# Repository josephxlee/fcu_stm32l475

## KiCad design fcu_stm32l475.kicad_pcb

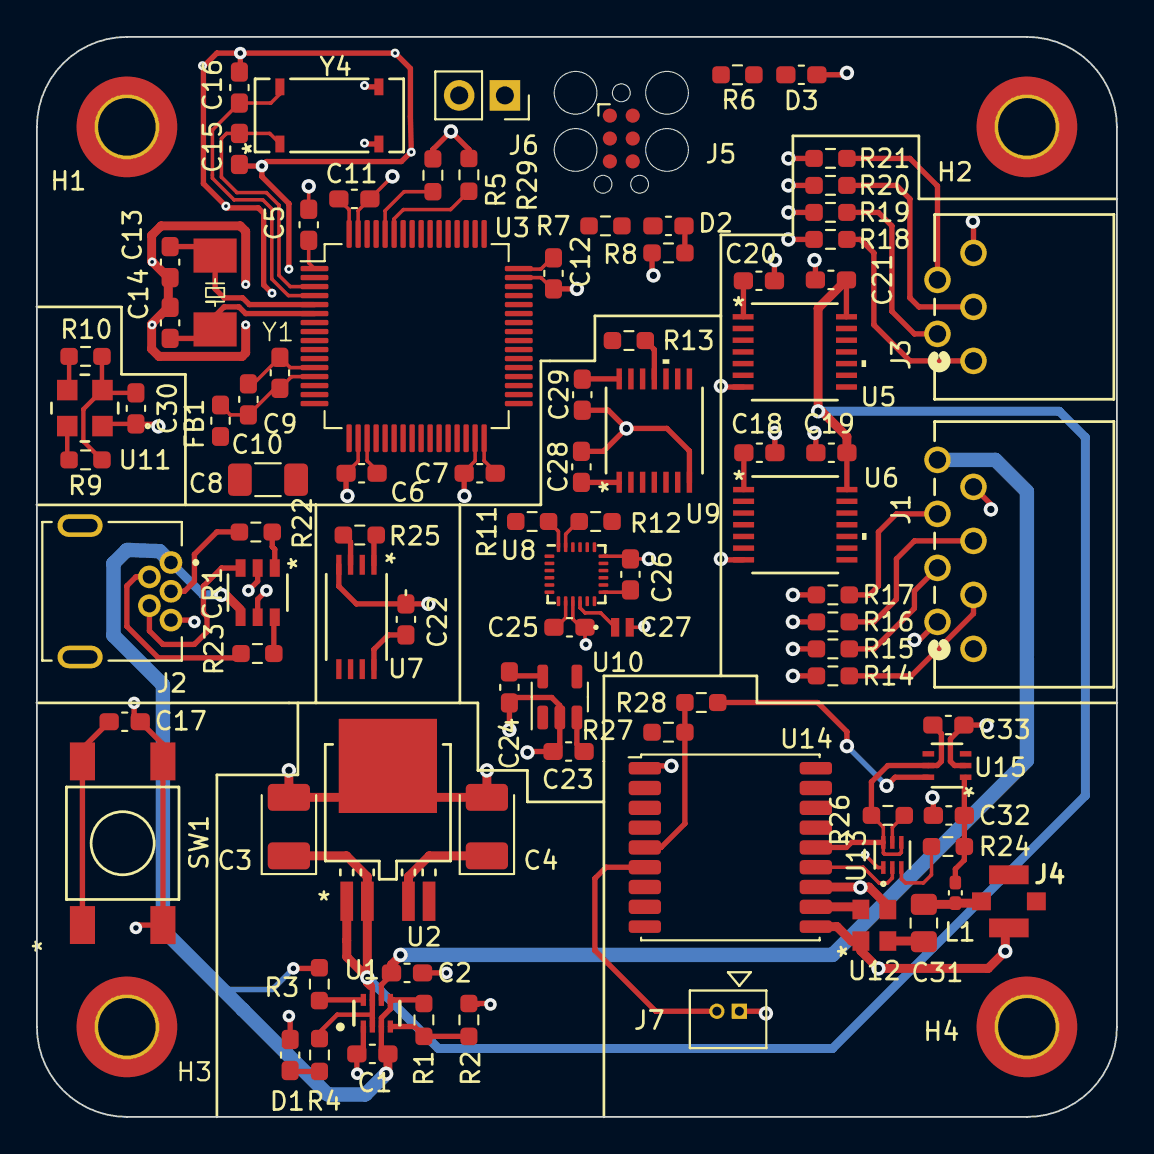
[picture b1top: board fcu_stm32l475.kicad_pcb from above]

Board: 4 copper layers, 60.0 x 60.0 mm, 96 parts (0 on the bottom side), 84 nets.

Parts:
C1, C2: 1uF,0603; C_0603_1608Metric_Pad1.08x0.95mm_HandSolder
C3, C4: 10uF,X5R,1210; CP_EIA-3528-21_Kemet-B_Pad1.50x2.35mm_HandSolder
C5, C6, C7, C11, C12, C18, C19, C20, C21, C22, C28, C29: 0.1uF; C_0603_1608Metric_Pad1.08x0.95mm_HandSolder
C8: 4.7uF; C_1206_3216Metric_Pad1.33x1.80mm_HandSolder
C9, C17: 0.01uF; C_0603_1608Metric_Pad1.08x0.95mm_HandSolder
C10: 1uF; C_0603_1608Metric_Pad1.08x0.95mm_HandSolder
C13, C14: 6pF,0603; C_0603_1608Metric_Pad1.08x0.95mm_HandSolder
C15, C16: 2pF,0603; C_0603_1608Metric_Pad1.08x0.95mm_HandSolder
C23, C24: 1uF, GRM155R70G105KA12D; C_0603_1608Metric_Pad1.08x0.95mm_HandSolder
C25, C26: 0.1uF, X7R, 06034C104KAT2A; C_0603_1608Metric_Pad1.08x0.95mm_HandSolder
C27: 0.1uF, CGBDT1X7T0E105M022BC; CAP_CGBDT_TDK
C30, C33: 0.1uF, 0603; C_0603_1608Metric_Pad1.08x0.95mm_HandSolder
C31: 47pF, C0805H470J3GACTU; C_0805_2012Metric_Pad1.18x1.45mm_HandSolder
C32: 10nF, C0603X103K4RACTU; C_0603_1608Metric_Pad1.08x0.95mm_HandSolder
CR1: ESDA6V1BC6; SOT23-6L_STM
D1: LS Q976-NR-1; C_0603_1608Metric_Pad1.08x0.95mm_HandSolder
D2: GREEN, LTST-C191KGKT; C_0603_1608Metric_Pad1.08x0.95mm_HandSolder
D3: LTST-C191KGKT; C_0603_1608Metric_Pad1.08x0.95mm_HandSolder
FB1: BEAD; L_0603_1608Metric_Pad1.05x0.95mm_HandSolder
H1, H2, H3, H4: MountingHole_Pad; MountingHole_3.2mm_M3_DIN965_Pad_TopBottom
J1: 292206-8
J2: GMSB0522152Y5EU
J3: 292206-5
J4: CONMHF1-SMD-G-T
J5: Conn_ARM_SWD_TagConnect_TC2030; Tag-Connect_TC2030-IDC-FP_2x03_P1.27mm_Vertical
J6: Conn_01x02_Pin; PinSocket_1x02_P2.54mm_Vertical
J7: 53047-0210; CON_530470210_MOL
L1: 27nH, LQG15HH27NJ02D; L_0402_1005Metric_Pad0.77x0.64mm_HandSolder
R1, R2, R3, R5, R9, R10, R11, R12, R14, R15, R16, R17, R18, R19, R20, R21, R25: 10K; R_0603_1608Metric_Pad0.98x0.95mm_HandSolder
R4, R6, R8: 330; R_0603_1608Metric_Pad0.98x0.95mm_HandSolder
R7, R27, R29: OPEN; R_0603_1608Metric_Pad0.98x0.95mm_HandSolder
R13, R22, R23, R28: 0; R_0603_1608Metric_Pad0.98x0.95mm_HandSolder
R24: 10, ERJ-UP3J100V; R_0603_1608Metric_Pad0.98x0.95mm_HandSolder
R26: 100K, ERJ-3GEYJ104V; R_0603_1608Metric_Pad0.98x0.95mm_HandSolder
SW1: FSM4JSMATR
U1: TPS2116DRLR
U2: TPS78533QKVUR
U3: STM32L475RCTx; LQFP-64_10x10mm_P0.5mm
U5, U6: TXU0104QPWRQ1
U7: AT25640B-XHL-T
U8: ICM-20948; InvenSense_QFN-24_3x3mm_P0.4mm
U9: TXS0104EPWR
U10: TPS7A0518PDBV; SOT-23-5
U11: LPS33KTR
U12: SF2352H; SF2316H
U13: SI1016X-T1-GE3
U14: MAX-M10S; ublox_MAX
U15: SN74LVC2G07DCKR
Y1: ECS-80-8-30-JGN-TR
Y4: ABS25-32.768KHZ-6-T

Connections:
+1V8: C24.1, C25.1, C28.2, R11.1, R12.1, U8.8 (VDDIO), U8.22 (~CS), U9.1 (VCCA), U9.8 (OE), U10.5 (OUT)
+3.3VA: C9.1, C10.1, FB1.2, U3.13 (VDDA)
+3V3: C4.1, C5.1, C6.1, C7.1, C8.1, C11.1, C12.1, C18.2, C20.2, C22.2, C23.1, C26.1, C29.1, C30.1, FB1.1, J6.1, R7.2, R9.1, R10.1, R25.1, U2.4 (OUT), U3.1 (VBAT), U3.19 (VDD), U3.32 (VDD), U3.48 (VDDUSB), U3.64 (VDD), U5.1 (VCCA), U6.1 (VCCA), U7.3 (*WP), U7.7 (*HOLD), U7.8 (VCC), U8.13 (VDD), U9.14 (VCCB), U10.1 (IN), U10.3 (EN), U11.2 (VDD), U14.7 (VCC_IO), U14.8 (VCC)
+5P: C2.1, J1.8, U1.6 (VIN2)
+5V: C3.1, C19.1, C21.1, R4.1, U1.2 (VOUT), U1.7 (VOUT), U2.1 (EN), U2.2 (IN), U5.14 (VCCB), U6.14 (VCCB)
/Connectors/BAT_SENS: J1.1, U3.10 (PC2)
/Connectors/NRST: J5.3 (~RESET), U3.55 (PB3)
/Connectors/PWM1_CH1: J1.3, R14.1, U6.13 (B1Y)
/Connectors/PWM1_CH2: J1.4, R15.1, U6.12 (B2Y)
/Connectors/PWM1_CH3: J1.5, R16.1, U6.11 (B3Y)
/Connectors/PWM1_CH4: J1.6, R17.1, U6.10 (B4Y)
/Connectors/PWM2_CH1: J3.1, R18.1, U5.13 (B1Y)
/Connectors/PWM2_CH2: J3.2, R19.1, U5.12 (B2Y)
/Connectors/PWM2_CH3: J3.3, R20.1, U5.11 (B3Y)
/Connectors/PWM2_CH4: J3.4, R21.1, U5.10 (B4Y)
/Connectors/TCK: J5.4 (SWCLK), U3.49 (PA14)
/Connectors/TMS: J5.2 (SWDIO), U3.46 (PA13)
/MCU/BARO_SCL: R10.2, U3.8 (PC0), U11.3 (SCL)
/MCU/BARO_SDA: R9.2, U3.9 (PC1), U11.4 (SDA)
/MCU/EEP_MISO: U3.22 (PA6), U7.2 (SO)
/MCU/EEP_MOSI: U3.23 (PA7), U7.5 (SI)
/MCU/EEP_NCS: R25.2, U3.50 (PA15), U7.1 (*CS)
/MCU/EEP_SCK: U3.21 (PA5), U7.6 (SCK)
/MCU/GNSS_EXTINT: R27.1, U3.27 (PB1)
/MCU/GNSS_RESET_N: U3.28 (PB2), U14.9 (~RESET)
/MCU/GNSS_RXD: U3.25 (PC5), U14.2 (TXD)
/MCU/GNSS_SAFEMODE_N: U3.33 (PB12), U14.18 (~SAFEBOOT)
/MCU/GNSS_SCL: U3.29 (PB10), U14.17 (SCL)
/MCU/GNSS_SDA: U3.30 (PB11), U14.16 (SDA)
/MCU/GNSS_TPULSE: U3.26 (PB0), U14.4 (TIMEPULSE)
/MCU/GNSS_TXD: U3.24 (PC4), U14.3 (RXD)
/MCU/IMU_FSYNC: R13.1, U9.11 (B3Y)
/MCU/IMU_INT1: U3.56 (PB4), U9.10 (B4Y)
/MCU/IMU_SCL: U3.61 (PB8), U9.12 (B2Y)
/MCU/IMU_SDA: U3.62 (PB9), U9.13 (B1Y)
/MCU/NRST: C17.1, J5.6 (SWO), SW1.1, SW1.2, U3.7 (NRST)
/MCU/PWM1_CH1: U3.14 (PA0), U6.2 (A1)
/MCU/PWM1_CH2: U3.15 (PA1), U6.3 (A2)
/MCU/PWM1_CH3: U3.16 (PA2), U6.4 (A3)
/MCU/PWM1_CH4: U3.17 (PA3), U6.5 (A4)
/MCU/PWM1_EN: U3.20 (PA4), U6.8 (OE)
/MCU/PWM2_CH1: U3.37 (PC6), U5.2 (A1)
/MCU/PWM2_CH2: U3.38 (PC7), U5.3 (A2)
/MCU/PWM2_CH3: U3.39 (PC8), U5.4 (A3)
/MCU/PWM2_CH4: U3.40 (PC9), U5.5 (A4)
/MCU/PWM2_EN: U3.36 (PB15), U5.8 (OE)
/MCU/SYS_KWUP2: J6.2, U3.2 (PC13)
/MCU/SYS_PVD_IN: R29.2, U3.59 (PB7)
/MCU/USB_OTG_FS_DN: CR1.6, R23.2, U3.44 (PA11)
/MCU/USB_OTG_FS_DP: CR1.1, R22.2, U3.45 (PA12)
/MCU/USB_OTG_FS_ID: CR1.3, J2.4 (ID), U3.43 (PA10)
/MCU/USR_LED: D2.2 (A), R7.1, U3.41 (PA8)
/PWR_SW_ST: R3.2, U1.8 (ST)
/Sensors/GNSS_ANT_OFF_N: U13.2 (G1), U14.13 (LNA_EN)
/Sensors/GNSS_ANT_SHORT_N: R28.1, U15.6 (1Y)
/Sensors/GNSS_EXT_INT: R27.2, R28.2, U14.5 (EXTINT)
/Sensors/GNSS_RF_IN: U12.4 (OUT), U14.11 (RF_IN)
/Sensors/GNSS_VCC_RF: C33.2, R26.2, U13.4 (S2), U13.6 (D1), U14.14 (VCC_RF), U15.5 (VCC)
/Sensors/IMU_FSYNC: U8.11 (FSYNC), U9.4 (A3)
/Sensors/IMU_INT1: U8.12 (INT1), U9.5 (A4)
/Sensors/IMU_SCL: R12.2, U8.23 (SCL/SCLK), U9.3 (A2)
/Sensors/IMU_SDA: R11.2, U8.24 (SDA/SDI), U9.2 (A1)
BOOT0: R5.2, U3.60 (BOOT0)
GND: C1.1, C2.2, C3.2, C4.2, C5.2, C6.2, C7.2, C8.2, C9.2, C10.2, C11.2, C12.2, C13.1, C14.1, C15.1, C16.1, C17.2, C18.1, C19.2, C20.1, C21.2, C22.1, C23.2, C24.2, C25.2, C26.2, C27.2, C28.1, C29.2, C30.2, C32.1, C33.1, CR1.2, CR1.5, D1.1 (K), D3.1 (K), H1.1, H2.1, H3.1, H4.1, J1.2, J1.7, J2.5 (GND), J3.5, J4.2 (Ext), J5.5 (GND), J7.1, R2.2, R5.1, R8.1, R14.2, R15.2, R16.2, R17.2, R18.2, R19.2, R20.2, R21.2, R29.1, SW1.3 (K), SW1.4 (A), U1.1 (GND), U2.3 (GND), U3.12 (VSSA), U3.18 (VSS), U3.31 (VSS), U3.47 (VSS), U3.63 (VSS), U5.7 (GND), U6.7 (GND), U7.4 (GND), U8.9 (SDO/AD0), U8.18 (GND), U8.20 (GND), U9.7 (GND), U10.2 (GND), U11.1 (GND), U12.1 (GND), U12.3 (GND), U13.1 (S1), U14.1 (GND), U14.10 (GND), U14.12 (GND), U15.2 (GND), Y4.2 (GND), Y4.3 (GND)
unnamed: D1.2 (A), R4.2
unnamed: D2.1 (K), R8.2
unnamed: D3.2 (A), R6.2
unnamed: J2.3 (D+), R22.1
unnamed: J2.2 (D-), R23.1
unnamed: C31.1, J4.1 (In), L1.1
unnamed: J5.1 (VCC), R6.1
unnamed: J7.2, U14.6 (V_BCKP)
unnamed: R1.2, R2.1, U1.4 (PR1)
unnamed: R13.2, U3.58 (PB6)
unnamed: C15.2, U3.3 (PC14), Y4.1
unnamed: C16.2, U3.4 (PC15), Y4.4
unnamed: C13.2, U3.5 (PH0), Y1.1
unnamed: C14.2, U3.6 (PH1), Y1.2
unnamed: C27.1, U8.10 (REGOUT)
unnamed: C31.2, U12.2 (IN)
unnamed: R24.2, U13.3 (D2)
unnamed: R26.1, U13.5 (G2)
unnamed: C32.2, L1.2, R24.1, U15.1 (1A)
U5V: C1.2, CR1.4, J2.1 (VBUS), R1.1, R3.1, U1.3 (VIN1), U1.5 (MODE), U3.42 (PA9)

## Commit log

2023-12-04 Initiate
